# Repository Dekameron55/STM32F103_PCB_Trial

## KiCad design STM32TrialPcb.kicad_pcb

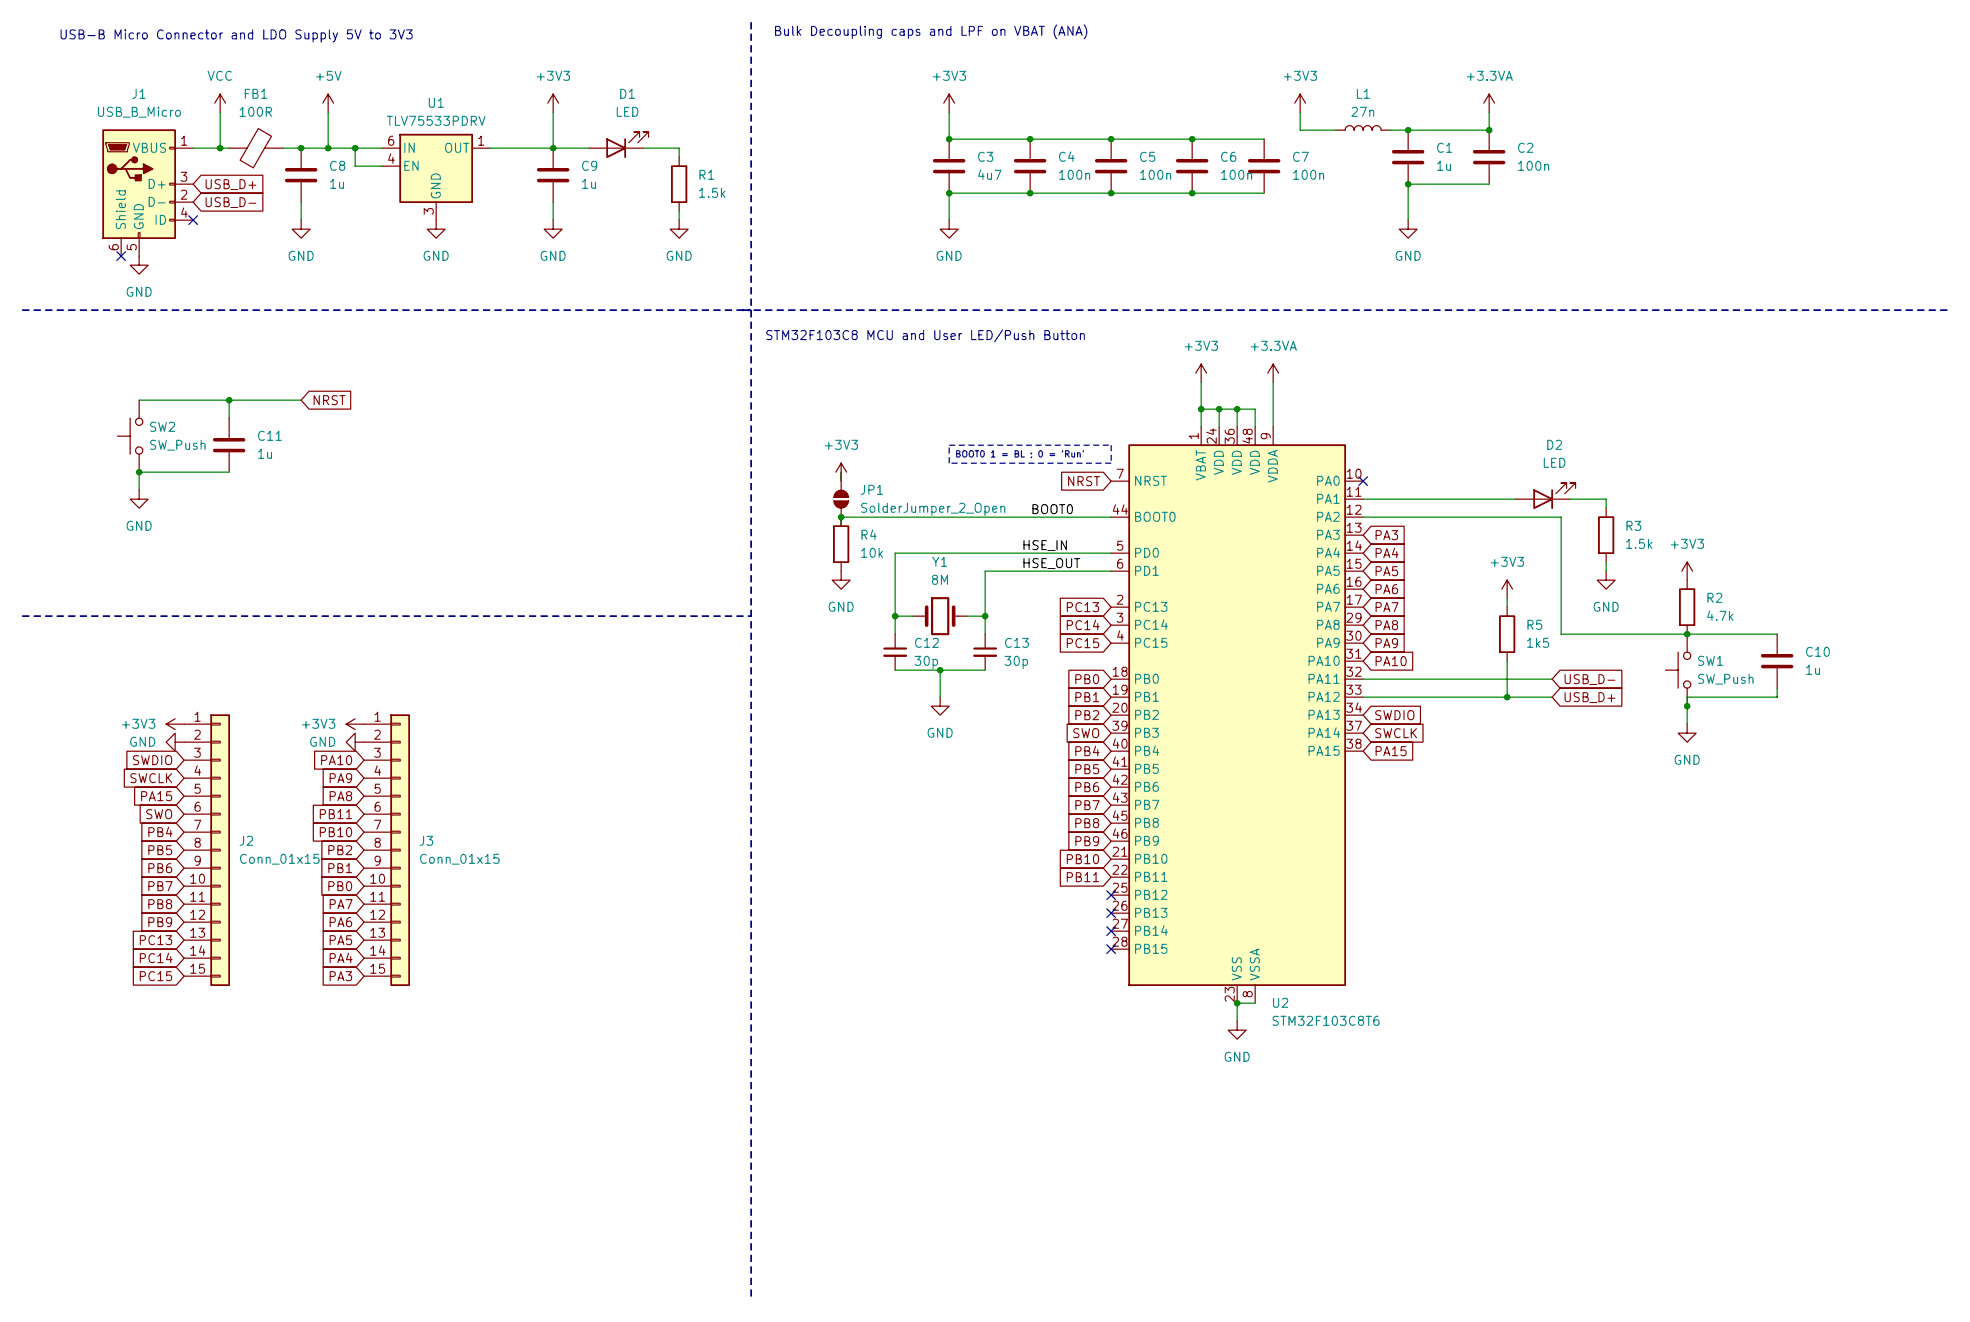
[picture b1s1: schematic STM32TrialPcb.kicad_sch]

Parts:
C1, C8, C9, C10, C11: 1u; C_0603_1608Metric
C2, C4, C5, C6, C7: 100n; C_0402_1005Metric
C3: 4u7; C_0603_1608Metric
C12, C13: 30p; C_0402_1005Metric
D1, D2: LED; LED_0603_1608Metric
FB1: 100R; L_0805_2012Metric
J1: USB_B_Micro; USB_Micro-B_Wuerth_629105150521
J2, J3: Conn_01x15; PinHeader_1x15_P2.54mm_Vertical
JP1: SolderJumper_2_Open; SolderJumper-2_P1.3mm_Open_Pad1.0x1.5mm
L1: 27n; L_0603_1608Metric
R1: 1.5k; R_0603_1608Metric
R2: 4.7k; R_0402_1005Metric
R3: 1.5k; R_0402_1005Metric
R4: 10k; R_0402_1005Metric
R5: 1k5; R_0402_1005Metric
SW1, SW2: SW_Push; SW_Push_SPST_NO_Alps_SKRK
U1: TLV75533PDRV; WSON-6-1EP_2x2mm_P0.65mm_EP1x1.6mm
U2: STM32F103C8T6; LQFP-48_7x7mm_P0.5mm
Y1: 8M; Crystal_SMD_5032-2Pin_5.0x3.2mm

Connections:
+3.3VA: C1.1, C2.1, L1.2, U2.9 (VDDA)
+3V3: C3.1, C4.1, C5.1, C6.1, C7.1, C9.1, D1.2 (A), J2.1, J3.1, JP1.2 (B), L1.1, R2.1, R5.1, U1.1 (OUT), U2.1 (VBAT), U2.24 (VDD), U2.36 (VDD), U2.48 (VDD)
+5V: C8.1, FB1.2, U1.4 (EN), U1.6 (IN)
/BOOT0: JP1.1 (A), R4.1, U2.44 (BOOT0)
/HSE_IN: C12.1, U2.5 (PD0), Y1.1
/HSE_OUT: C13.1, U2.6 (PD1), Y1.2
GND: C1.2, C2.2, C3.2, C4.2, C5.2, C6.2, C7.2, C8.2, C9.2, C10.2, C11.2, C12.2, C13.2, J1.5 (GND), J2.2, J3.2, R1.2, R3.2, R4.2, SW1.1, SW2.1, U1.3 (GND), U1.7 (GND), U2.8 (VSSA), U2.23 (VSS), U2.35 (VSS), U2.47 (VSS)
NRST: C11.1, SW2.2, U2.7 (NRST)
unnamed: D1.1 (K), R1.1
unnamed: D2.2 (A), U2.11 (PA1)
unnamed: D2.1 (K), R3.1
unnamed: C10.1, R2.2, SW1.2, U2.12 (PA2)
PA3: J3.15, U2.13 (PA3)
PA4: J3.14, U2.14 (PA4)
PA5: J3.13, U2.15 (PA5)
PA6: J3.12, U2.16 (PA6)
PA7: J3.11, U2.17 (PA7)
PA8: J3.5, U2.29 (PA8)
PA9: J3.4, U2.30 (PA9)
PA10: J3.3, U2.31 (PA10)
PA15: J2.5, U2.38 (PA15)
PB0: J3.10, U2.18 (PB0)
PB1: J3.9, U2.19 (PB1)
PB2: J3.8, U2.20 (PB2)
PB4: J2.7, U2.40 (PB4)
PB5: J2.8, U2.41 (PB5)
PB6: J2.9, U2.42 (PB6)
PB7: J2.10, U2.43 (PB7)
PB8: J2.11, U2.45 (PB8)
PB9: J2.12, U2.46 (PB9)
PB10: J3.7, U2.21 (PB10)
PB11: J3.6, U2.22 (PB11)
PC13: J2.13, U2.2 (PC13)
PC14: J2.14, U2.3 (PC14)
PC15: J2.15, U2.4 (PC15)
SWCLK: J2.4, U2.37 (PA14)
SWDIO: J2.3, U2.34 (PA13)
SWO: J2.6, U2.39 (PB3)
USB_D+: J1.3 (D+), R5.2, U2.33 (PA12)
USB_D-: J1.2 (D-), U2.32 (PA11)
VCC: FB1.1, J1.1 (VBUS)

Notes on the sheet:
BOOT0 1 = BL ; 0 = 'Run'
Bulk Decoupling caps and LPF on VBAT (ANA)
STM32F103C8 MCU and User LED/Push Button
USB-B Micro Connector and LDO Supply 5V to 3V3

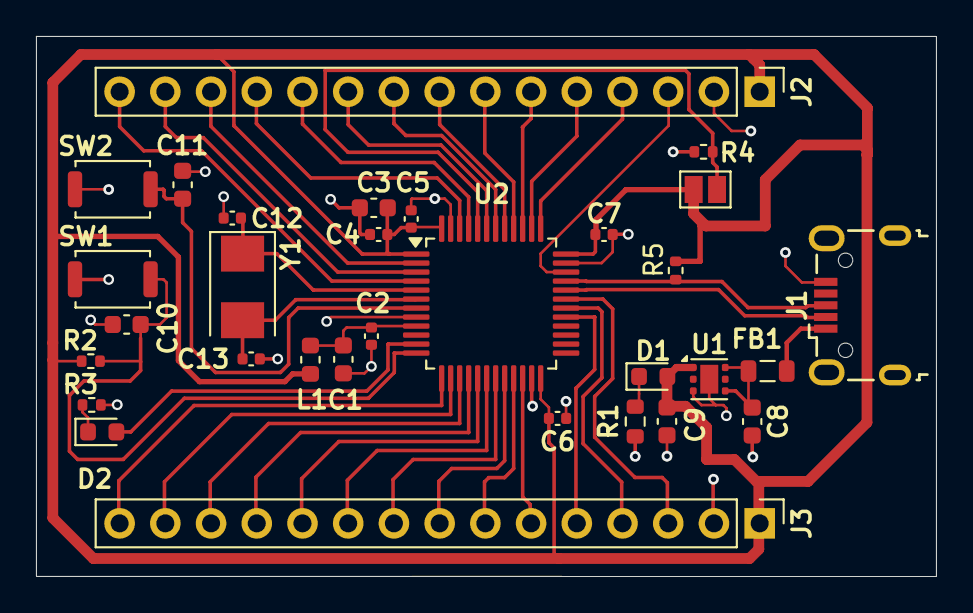
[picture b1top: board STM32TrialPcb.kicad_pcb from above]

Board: 2 copper layers, 50.0 x 30.0 mm, 31 parts (0 on the bottom side), 41 nets.

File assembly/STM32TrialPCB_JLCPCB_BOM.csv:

Comment,Designator,Footprint,LCSC PN
SW_Push,"SW2,SW1",SW_Push_SPST_NO_Alps_SKRK,C115357
LED,"D1,D2",LED_0603_1608Metric,C2286
10k,R4,R_0402_1005Metric,C25531
100nF,"C5,C7,C2,C4,C6",C_0402_1005Metric,C1525
27nH,L1,L_0603_1608Metric,C12100
1.5k,R3,R_0402_1005Metric,C25930
1uF,"C8,C1,C9,C10,C11",C_0603_1608Metric,C1592
100R,FB1,L_0805_2012Metric,C1015
STM32F103C8T6,U2,LQFP-48_7x7mm_P0.5mm,C8734
8M,Y1,Crystal_SMD_5032-2Pin_5.0x3.2mm,C115962
4.7uF,C3,C_0603_1608Metric,C1705
4.7k,R2,R_0402_1005Metric,C25900
30pF,"C12,C13",C_0402_1005Metric,C277479
1.5k,R1,R_0603_1608Metric,C22843
1.5k,R5,R_0402_1005Metric,C25867
USB_B_Micro,J1,USB_Micro-B_Wuerth_629105150521,C2894326
TLV75533PDRV,U1,WSON-6-1EP_2x2mm_P0.65mm_EP1x1.6mm,C2861750

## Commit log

2024-12-21 Initial commit cleaning up todo
2024-12-21 Dir clean up, update readme, add pdf schematic
2024-12-21 Move gerbers and drill files add pdf scematic
2024-12-21 add a sample screenshot
2025-01-11 Improve layout, dimensions, symmetry.
2025-01-11 fix dimensions 50x30mm etc...
2025-01-18 add assembly and move gerbers, update pcb
2025-01-18 update screenshot
